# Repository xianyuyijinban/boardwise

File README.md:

# boardwise

English | [中文](#中文)

An agent harness for hardware engineers.

It lets an AI assistant (Claude Code, DeepSeek, Kimi Code — any of them)
actually read your schematic — components, nets, pins, not screenshots —
and do real work on it: review the board, mark the problems, edit with
your sign-off, export the fab files. EasyEDA Pro is the platform we know
inside-out today; KiCad is next, and the architecture has been
multi-platform from day one.

## What it does

**Review.** With the editor open, one command:

```bash
boardwise checkup
```

You get a report: ERC/DRC, 23 design rules, which parts
still lack datasheets, and every finding pointing at a concrete
component, pin and net — with markers drawn on the canvas where the
problems are. On real boards it has caught things the designer had
missed — a current-sense circuit with no bias, that kind of problem.
You don't find those by matching rules against a netlist; you have to
check whether the architecture makes sense together. When a rail's
voltage lives only in your head, `intent audit` lists those nets and
asks once; the answer lands in a design-intent contract
(`intent set-rail`) and is never asked again. The PCB review stages
already landed have flagged real layout defects on real boards — a
motor driver's exposed pad whose copper pour was left as a thermal
island on a four-layer FOC driver, that class of problem.

**Edit.** Find a problem, get a change preview; nothing moves until you
approve; afterwards it reads back and re-reviews to confirm the problem
is actually gone. Edit kinds today: change a component value, add a
missing part, repair a single pin connection, insert an RC/divider
subcircuit, move a functional block.

**Export.** One `export-fab` writes the whole fab bundle — Gerber,
pick-and-place and BOM together. (There is no netlist export command;
the netlist is read internally for review, not written out as a file.)

**Draw.** You state the circuit intent — a divider, an RC low-pass, an
LDO; parts, values, which pin joins which net — and the drawing
compiler turns it into a sheet a human can read: where parts sit, how
wires run, where text goes so it doesn't sit on a wire. Wrong
connectivity, not enough room, a conflict with your locked placement —
it refuses rather than hand you a bad drawing. It compiles offline, and
it can also land into the open editor itself — placement, pin readback
before any wire, save, and a render of the result. Several modules
compose onto one page: what is already on the page becomes keep-outs,
your locked placements are honoured, every rail gets a flag, and one
`draw discard` takes a landed page back off.

Newer pieces worth knowing:

- **Offline geometry render** — `checkup --file` draws each board to
  `canvas-<board>.svg` (two views, findings highlighted); it is drawn from the
  archived geometry, not a screenshot.
- **`parts accept-unknown`** — an engineer puts on record that a part's unknowns
  are acceptable, so the datasheet gate stops owing it; it is **not** a pass, and
  the conclusion still counts the accepted parts.
- **KiCad bare net ids** — a `(net 3)` with no name is read (as `net#3`) instead
  of the whole board being refused for carrying no net names.
- **Staged, interruptible review** — after **one** `checkup` the first checkpoint
  (`initial`/`partial`: environment and versions, `report.conclusion`, ERROR / host
  DRC, open items, artifact paths) is delivered **before** any deeper digging; deeper
  work then runs in small batches (at most 3 findings each). An existing report can be
  read again instead of re-run, and an aborted run is summarised as `partial` from what
  is already on disk. The first-checkpoint order and the global recompute dedupe are
  still **process constraints, not runtime gates** — see `docs/review-sop.md` §3.0a.
  Nothing here is claimed to be enforced by the tool automatically.

## Architecture and roadmap

Three layers, all on your own machine — nothing goes through a cloud:

```
AI assistant
  │  calls short commands (CLI / skill / dsh plugin)
  ▼
offline engine      parse · review rules · drawing compiler · change plans
  │  loopback only
  ▼
daemon + editor extension      reads design data; writes go preview → approve → readback
  ▼
EasyEDA Pro (today) · KiCad (planned)
```

Standing rules: the checks and the delivery validation live in tools;
orchestration constraints that have no runtime gate yet are disclosed in the SOP as
exactly that; every conclusion carries evidence; writes are preview → authorize → readback;
on a timeout or disconnect it reads back first and never blindly
retries.

| Stage | Status |
|---|---|
| Schematic review (rule families + datasheet gate + eval harness) | Usable, in maintenance |
| Review-to-local-edit (preview / authorize / readback / re-review) | Usable |
| Drawing compiler (divider / RC / LDO / IC periphery / power entry) | Modules and multi-module pages land in the editor; flyback (UC3845) lands on-page from locked placements with rail/ground flags, lint-clean; free auto-placement is still below the bar we hold it to |
| PCB review (DRC closure → module-by-module layout → device checks) | Stages A–D done (loop/return-path, power, MCU, FOC rule packs) — stage E (device checks + report) not started; roadmap in `tasks/122-pcb-review-roadmap.md` |
| Full schematic capture → PCB generation → SPICE simulation | In that order |
| KiCad platform | Planned |

One sentence on how the review rules are scored: the annotated eval
sets are signed and split into a tuning pile and an acceptance pile,
and the harness is built so the acceptance pile cannot leak into the
scores — `--split` defaults to `dev` and holdout records enter no
denominator. Two tuning constants predate the split discipline; their
comments declare their evidence boards, and
`tests/test_doc_claims.py` keeps this paragraph honest.
Details in `outputs/017_generalization.md`.

## Install & supported environments

Three artifacts in [Releases](https://github.com/xianyuyijinban/boardwise/releases):

| File | For |
|---|---|
| `boardwise-windows-x.x.x.exe` | Anyone who doesn't want Python: single-file CLI, part library embedded |
| `boardwise-connector-x.x.x.eext` | Everyone: the extension you import into EasyEDA |
| `boardwise-dsh-x.x.x.tgz` | DeepSeek users: the dsh plugin, optional |

Environment: Windows. Python ≥ 3.10 (source installs only; 3.9 and
below are not supported). EasyEDA Pro **3.2.149 / 3.2.186 / V4.1.60**
are all verified on real machines; older versions are not guaranteed.
macOS/Linux are untested — the offline review probably runs, the bridge
is unverified.

Fastest path: [`docs/install.md`](docs/install.md) (Chinese — every
step says what you should see). For the impatient: `pip install .` →
import the `.eext` in the editor → `boardwise doctor` all green →
`boardwise checkup`.

Getting the review checklist into your AI: `boardwise install-skill`
installs it for Kimi Code and Claude Code (one side only: `--harness kimi`
or `--harness claude`; a different file already there is backed up to
`SKILL.md.bak-<YYYYMMDD-HHMMSS>`, never quietly replaced, and a second
install on the same day gets its own file rather than displacing the first).
Using another agent —
Codex, Hermes, anything? `boardwise install-skill --agent` prints a short
prompt to paste into your AI, and it puts the file where it looks for
skills, which it knows better than we do. If your AI is working inside a
clone of this repo, [`AGENTS.md`](AGENTS.md) already points it at the
checklist — nothing to install.

## Common errors & notes

- **Nothing connects** — nine times out of ten it's one of three: the
  daemon isn't running, the extension's
  *external interaction* permission wasn't granted, or the extension
  never activated. The extension's **About…** menu tells you which.
  The daemon is the one that looks after itself: any command that needs
  the bridge starts one that isn't there and waits for it (the log it
  writes is `${BOARDWISE_HOME:-~/.boardwise}/log/daemon-<date>.log`, and
  the failure it prints names it). If it still is not up, run
  `boardwise bridge start` in the foreground and read what it says;
  `BOARDWISE_NO_AUTO_DAEMON=1` turns the automatic start off for the
  setups that manage it themselves.
- **Several project windows open** — name one: `--project <name>`. It
  refuses to guess.
- **Encrypted `.epro2` export** — unreadable; re-export with encryption
  off.
- **A `.eprj2` file holds no drawing** — it's just the project shell.
  Read live through the bridge, or export an `.epro2` backup.
- **Exit code 3 is not "the board is clean"** — it means the online
  state could not be stated. Whatever could not run is marked
  `{checked: false}` with no counts.
- **It always previews before touching your drawing.** Don't skip the
  confirmation out of habit — the readback after your yes is the point,
  not the ceremony.
- Canvas screenshots return a cached frame on 3.2.186 — use the OS
  snipping tool when you need a real one.

## Acknowledgments

We're glad these projects exist:

- [easyeda-agent](https://github.com/zhoushoujianwork/easyeda-agent)
  (zhoushoujianwork) — our thanks for the ideas and the inspiration in
  the details. It is their continued progress that let us sidestep the
  pitfalls and reach our own goals faster and more efficiently.
- [@jlceda/pro-api-types](https://www.npmjs.com/package/@jlceda/pro-api-types) —
  the official API type definitions the connector stands on.
- The EasyEDA team — opening real extension APIs to the community is
  what makes any of this possible. Thank you.

## License

MIT

---

## 中文

硬件工程师的 Agent Harness。

让 AI 助手（Claude Code、DeepSeek、Kimi Code……哪个都行）真正读懂你的
原理图——器件、网络、引脚，不是截图——然后替你干活：审板子、标问题、
按你的授权改图、导出制板文件。目前吃透的是立创 EDA 专业版，KiCad 是
下一个平台，架构从一开始就按多平台设计。

### 它能做什么

**审板子。** 编辑器开着，一条命令：

```bash
boardwise checkup
```

输出一份报告：ERC/DRC、23 条设计规则、哪些器件还缺数据手册、每条问题
各自指着具体的器件、引脚和网络；顺手把问题标记在画布上。它在真板子上
抓到过设计者自己没注意到的问题——比如一个该做偏置而没做的电流采样
电路。这类问题不是查规则书能查出来的，得先理解整个架构自不自洽。
有些电源网的电压只在你脑子里——`intent audit` 会把这些网列出来问一次，
答案用 `intent set-rail` 写进设计意图契约，以后不再问。PCB 审查已落地的
阶段也在真板子上抓到过真缺陷：一块四层 FOC 驱动板上，电机驱动器的
散热焊盘铺铜成了孤岛。

**改图。** 发现问题后，它给修改预览，你点头它才动，动完自己回读、再跑
一遍审查确认问题真的消失。已经支持的改法：改器件值、补一颗缺失的器件、
修单个引脚连接、插入 RC/分压子电路、局部移动一个功能块。

**导出。** 一条 `export-fab` 同时出 Gerber、坐标文件和 BOM 三样。
（网表没有单独的导出命令；它在内部读取供审查，不落文件。）

**画图。** 你写电路意图——分压、RC 低通、LDO，器件、参数、哪个脚接
哪个网——画法编译器负责把它变成一张能给人看的图：器件怎么摆、线怎么
走、字放哪不压线。接法错、空间不够、和你的锁定冲突，它宁可拒绝也不交
出一张烂图。离线出图之外，它已经能直接落进开着的编辑器——放件、
拉线前先回读引脚、保存、再出一张渲染图。多个模块能组合进同一页：
页上已有的图元自动变成禁布区、你锁定的位置被尊重、每条电源轨都有
旗标，一条 `draw discard` 能把落好的整页撤下来。

几件新东西值得知道：

- **离线几何渲染**——`checkup --file` 给每块板出 `canvas-<board>.svg`（顶/底两个
  视窗、finding 高亮）；它是按归档几何**画**出来的，不是截图。
- **`parts accept-unknown`**——工程师当面记下「这颗器件的未知我接受」，数据手册闸
  不再欠它；它**不是审过**，结论里照样数着这些被接受的器件。
- **KiCad 裸网序号**——没有名字的 `(net 3)` 照读（记成 `net#3`），不再因为一块板
  网名全丢就整盘读不出来。
- **分阶段、可中断的审查**——**一次** `checkup` 之后，先把首轮检查点
  （`initial`/`partial`：环境与版本、`report.conclusion`、ERROR / 宿主 DRC、待确认项、
  产物位置）交付出去，再分批深挖；每批最多 3 条 finding。已有报告可以复读而不必重跑，
  中止的 run 基于已在盘上的产物整理成 `partial`。首轮顺序与「全局重算去重」目前仍是
  **流程约束，不是运行时硬闸**——见 `docs/review-sop.md` §3.0a。这里没有一句说工具会
  自动执行它。

### 架构和规划

三层，全跑在你自己电脑上，不经过任何云端：

```
AI 助手
  │  调很短的命令（CLI / skill / dsh 插件）
  ▼
离线引擎      解析工程文件 · 审查规则 · 画法编译 · 修改计划
  │  本机回环
  ▼
daemon + 编辑器扩展      读工程数据，写之前先预览、你授权、它回读
  ▼
立创 EDA 专业版（现在） · KiCad（规划）
```

规矩就几条：**检查与交付校验**住在工具里；**尚未形成硬闸的编排约束**在 SOP 里明确
披露，不当成工具已自动执行；每个结论带证据；
写操作一律预览 → 授权 → 回读；超时断连先读回，绝不盲目重试。

路线图：

| 阶段 | 状态 |
|---|---|
| 原理图审查（规则族 + 数据手册闸 + 评测体系） | 可用，维护中 |
| 审查到局部修改（预览/授权/回读/复查） | 可用 |
| 画法编译器（分压/RC/LDO/IC 外围/电源入口） | 单模块与多模块整页均已能落进编辑器；反激（UC3845）带锁定落点+电源/地旗标已能落页且 lint 零错误；自由自动摆放目前达不到我们要求的及格线 |
| PCB 审查（DRC 闭环 → 按模块布局 → 器件检查） | A–D 阶段完成（环路/回流路径、电源、MCU、FOC 规则包），E 阶段（器件检查+报告整合）未开——路线图见 `tasks/122-pcb-review-roadmap.md` |
| 完整原理图绘制 → PCB 生成 → SPICE 仿真 | 按序推进 |
| KiCad 平台 | 规划中 |

审查规则的评测方式说一句人话：我们有一套签名标注过的评测集，分成
调参用和验收用两摞；harness 在结构上堵死验收摞混进分数——`--split` 默认
`dev`，验收摞不进任何分母。有两条调参常量先于分堆制度诞生，它们的注释
里写明了取证板，`tests/test_doc_claims.py` 盯着这段话不许它过期。
细节在 `outputs/017_generalization.md`。

### 安装包和环境支持

[Releases](https://github.com/xianyuyijinban/boardwise/releases) 里三样：

| 文件 | 给谁 |
|---|---|
| `boardwise-windows-x.x.x.exe` | 不想装 Python 的人：单文件 CLI，器件库已内嵌 |
| `boardwise-connector-x.x.x.eext` | 所有人：立创 EDA 里导入的扩展 |
| `boardwise-dsh-x.x.x.tgz` | DeepSeek 用户：dsh 插件，可选 |

环境：Windows；Python ≥ 3.10（仅开发/源码安装需要，3.10 以下不支持）；
立创 EDA 专业版 **3.2.149 / 3.2.186 / V4.1.60** 都真机验证过，更低版本
不保证。macOS/Linux 没测过——理论上离线审查能跑，桥没验证。

最快的路：`docs/install.md`（给朋友看的版本，全程中文，每步写了
"应该看到什么"）。熟手：`pip install .` → 编辑器导入 `.eext` →
`boardwise doctor` 全绿 → `boardwise checkup`。

把审查清单装进你的 AI：`boardwise install-skill` 给 Kimi Code 和 Claude Code 装上
（只装一侧加 `--harness kimi` 或 `--harness claude`；目标位置已有别的版本会先备份成
`SKILL.md.bak-<年月日-时分秒>`，不会静默覆盖；同一天装两次是两个备份文件，第二个不覆盖第一个）。用的不是这两个 agent——Codex、Hermes
之类——跑 `boardwise install-skill --agent`：它打印一段引导指令，粘给你在用的 AI，
放哪儿由它自己定，它比我们清楚。AI 就在本仓库 clone 里干活的话，根目录
[`AGENTS.md`](AGENTS.md) 已经指到了清单，不用装。

### 常见错误和注意事项

- **连不上**，九成是三件事之一：daemon 没起、
  扩展的"外部交互"权限没给、扩展没激活。扩展菜单里的 **About…** 会直接
  告诉你卡在哪步。daemon 这一条现在会自己解决：任何需要桥的命令发现它不在，
  自己把它拉起来并等它就绪（它的输出写在
  `${BOARDWISE_HOME:-~/.boardwise}/log/daemon-<日期>.log`，拉起失败时报错会点名这个文件）。
  还是没起来就跑 `boardwise bridge start`（前台运行，原因直接打在窗口里）；
  自己管 daemon 的部署（计划任务/服务）用 `BOARDWISE_NO_AUTO_DAEMON=1` 关掉自动拉起。
- **开了好几个工程窗口**：命令要指名，`--project <名字>`，否则它拒绝猜。
- **`.epro2` 导出时勾了加密**：读不了，重新导一次别勾加密。
- **`.eprj2` 单文件里没有图纸**：那只是工程壳，图纸要么在线走桥读，
  要么导出 `.epro2` 备份。
- **退出码 3 不是"板子干净"**：是**说不清**——在线状态读不出来（daemon 没起、扩展没连上），
  或者 `completion.verdict` 是 `incomplete`（没读到模型 / 有器件缺手册未审 / 骨架没生成 /
  覆盖有缺口）。`review --live` 拿到了模型、但模型是空的（0 器件 0 网络）也算（075）——
  它与"根本没拿到模型"是两句话，两句都不许读成通过。审查没跑成的部分报告里会写
  `{checked: false}`，不带计数。**CI 里别把 3 当通过**（073 起 `review` / `checkup` 都这样；
  有 ERROR 仍是 1，`complete-with-open-items` 仍是 0）。
- **它要改你的图之前**一定会先给预览，别图快跳确认——确认完它自己
  还会回读验证，这一步省不掉也不该省。
- 画布截图在 3.2.186 上返回的是缓存帧，要真实截图请用系统截图工具。

### 致谢

站在这些项目的肩膀上，我们很庆幸它们存在：

- [easyeda-agent](https://github.com/zhoushoujianwork/easyeda-agent)（zhoushoujianwork）——
  感谢 EasyEDA-Agent 提供的一些思路和细节上的灵感。正是他们的不断前进，
  才让我们少踩了坑，能够以更高效、更快速的方式接近自己的目标。
- [@jlceda/pro-api-types](https://www.npmjs.com/package/@jlceda/pro-api-types)——
  官方 API 类型定义，connector 开发站在它上面。
- 立创 EDA 团队——愿意把扩展接口真正开放给社区，这个项目才有机会存在。谢谢。

### License

MIT

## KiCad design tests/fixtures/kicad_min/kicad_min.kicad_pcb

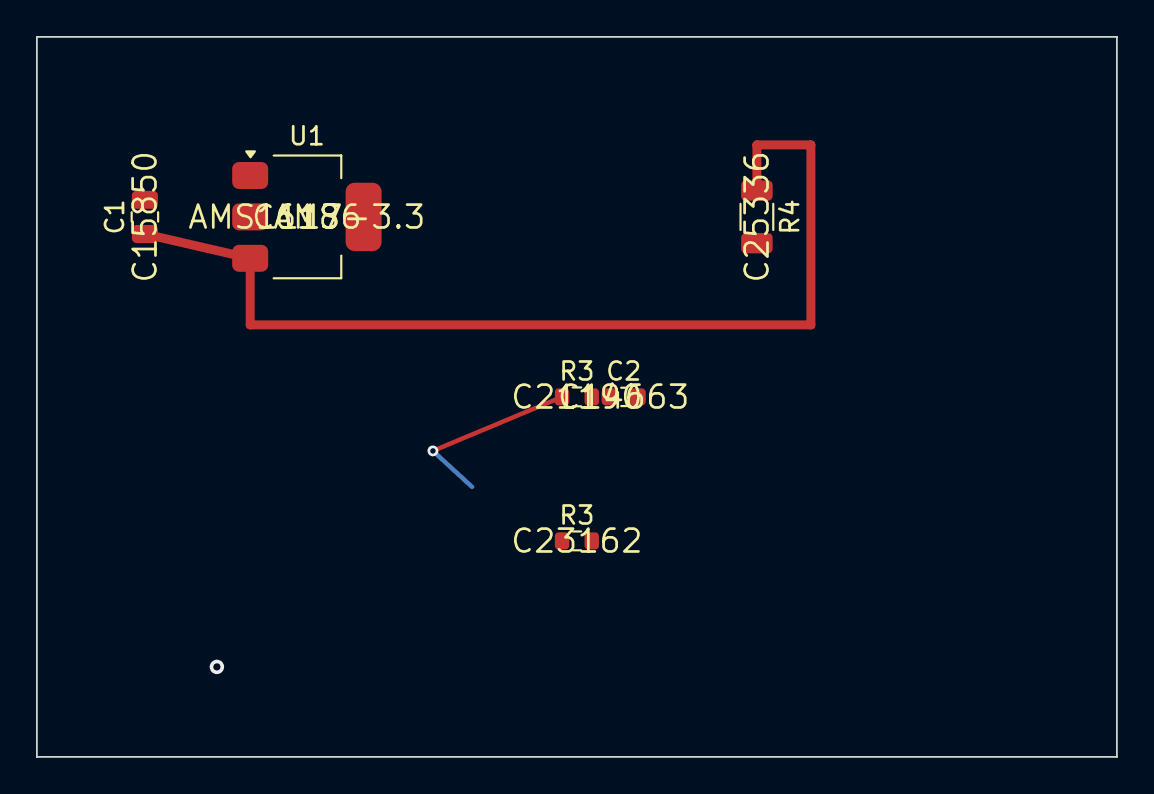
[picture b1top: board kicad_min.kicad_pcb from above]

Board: 2 copper layers, 60.0 x 40.0 mm, 7 parts (1 on the bottom side), 4 nets.

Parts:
C1: 10uF; C_0805_2012Metric
C2: 100nF; C_0603_1608Metric
R1: 10k; R_0603_1608Metric
R3: 4.7k; R_0603_1608Metric
R3#2: 1k; R_0603_1608Metric
R4: 0.01; R_1206_3216Metric
U1: AMS1117-3.3; SOT-223-3_TabPin2

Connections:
+3V3: C2.1, R1.1, R3.1, U1.2 (VO)
+5V: C1.1, R4.1, U1.3 (VI)
GND: C1.2, C2.2, R3#2.2, U1.1 (GND)
LED_A: R1.2, R3#2.1

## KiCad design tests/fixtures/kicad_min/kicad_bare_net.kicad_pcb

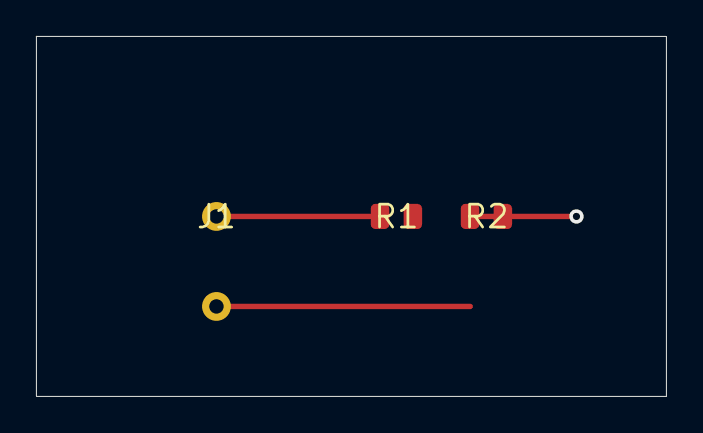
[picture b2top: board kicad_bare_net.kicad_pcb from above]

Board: 2 copper layers, 35.0 x 20.0 mm, 3 parts (0 on the bottom side), 2 nets.

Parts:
J1: Screw_Terminal; Screw_Terminal_01x02
R1: 60.4; R_0805_2012Metric
R2: 120; R_0805_2012Metric

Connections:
CAN_H: J1.1, R1.1
CAN_L: J1.2, R2.2
